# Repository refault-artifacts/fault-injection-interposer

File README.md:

# Interposer PCB for DDR5 UDIMMs
Hardware files for the fault injection interposer of
REFault: A Fault Injection Platform for Rowhammer Research on DDR5 Memory.

The interposer consists of a 6-layer PCB that can be used in between an off-the-shelf
DDR5-compatible motherboard and an DDR5 SDRAM UDIMM. Some signals
can be forced high or low by an external control signal to inject
or suppress certain DRAM commands.

## Design
The schematic and PCB was designed in KiCAD. Open `hardware/udimm_interposer.kicad_pro` in KiCAD 8 or later to view the design files.
From there, you should be able to select the schematic and PCB layout.

For convenience, you can also find a PDF version of the schematic in `docs/schematic.pdf`. A bill of materials (BOM) is also provided in `docs`.

## Manufacturing
The PCBs were manufactured by JLCPCB and were assembled by hand.
It is reasonable to also order an SMT stencil, so soldering is easier.
The Gerber files needed for manufacturing are located at `hardware/output`.

### Impedance Control
The PCB is impedance controlled. It uses the JLC06121H-1080 stackup options.

### Manufacturing options
| Option | Value |
|--------|-------|
|Base Material| FR-4|
|Layers| 6|
|Dimension| 133.4 mm * 21.9 mm|
|Product Type| Industrial/Consumer electronics|
|Different Design| 1|
|Delivery Format| Single PCB|
|PCB Thickness| 1.2|
|Impedance Control| yes JLC06121H-1080|
|Layer Sequence||
|PCB Color| Green|
|Silkscreen| White|
|Via Covering| Tented|
|Surface Finish| ENIG|
|Deburring/Edge rounding| No|
|Outer Copper Weight| 1|
|Inner Copper Weight| 0.5|
|Gold Fingers| Yes|
|Flying Probe Test|Fully Test|
|Castellated Holes|no|
|Remove Order Number|No|
|Min hole size/diameter|0.3/0.4mm|
|4-Wire Kelvin Test|No|
|Material Type|FR4-Standard TG 135-140|
|Paper between PCBs|No|
|Appearance Quality|IPC Class 2 Standard|
|Confirm Production file|Yes|
|Silkscreen Technology|Ink-jet/Screen Printing Silkscreen|
|Package Box|With JLCPCB logo|

**Important**: For future orders, it may be a better idea to not select "Gold Fingers",
because we do not want chamfering along the edge connector. As far as
the PCB manufacturer is concerned, the edge connector consists of normal
pads. Otherwise add an explicit remark that you do not want any chamfering.

## Assembly
Assembly can be done manually using a stencil (ordered with the PCB),
some solder paste and a hot air gun. The connector on top was soldered
manually.
### Bill of Materials (BOM)
See docs/bom

### Verification
To ensure that there are no shorts between pins and all pins are properly
soldered, a continuity check should be performed prior to testing
the module more thoroughly with e.g. Memtest86+.

## Known Issuses
Since the UDIMM connector is comparatively long, the PCB might experience
thermal warping along the length of the connector, lifting the PCB away
from the connectors of the DIMM. For this reason, the connector was soldered
on manually.

### Modifications
Some switches are not connected to the flat flex connector.
To hard-wire them to the "passthrough" position, a wire must be soldered
to the appropriate pads on the voltage regulator side of the PCB.
Check the schematic and design files for details.

## License
Some parts of the PCB may be subject to copyright of third parties
(e.g. 3D models provided by manufacturer).
Otherwise, the design is released under MIT License.

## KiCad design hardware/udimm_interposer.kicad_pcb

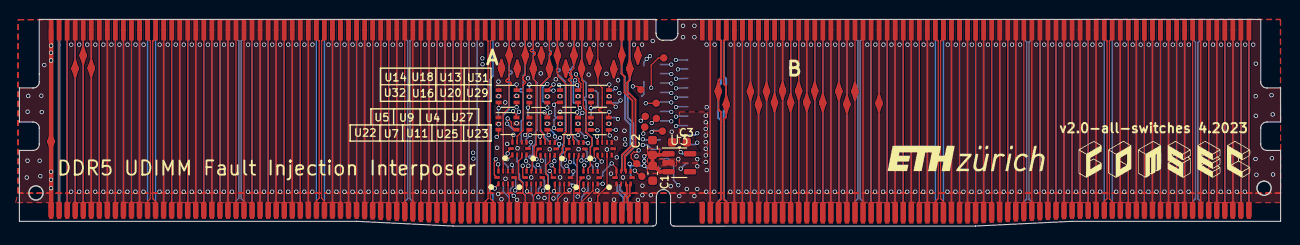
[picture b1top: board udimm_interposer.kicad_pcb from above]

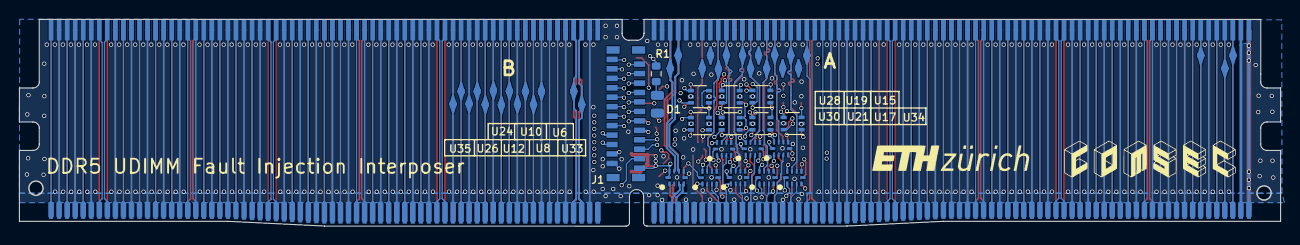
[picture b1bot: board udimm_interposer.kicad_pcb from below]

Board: 6 copper layers, 133.3 x 21.9 mm, 119 parts (50 on the bottom side), 225 nets.

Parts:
C1, C3: 100n; C_0603_1608Metric
C2: 2.2u; C_0603_1608Metric
D1: APHCM2012CGCK-F01; LED_0805_2012Metric
J1: Molex 5019512430; 5019512430
R1: 330; R_0603_1608Metric
TP1: VIN_BULK; testpoint
TP2: HSCL; testpoint
TP3: HSDA; testpoint
TP4, TP6, TP9, TP12, TP15, TP17, TP20, TP23, TP27, TP43, TP46, TP49, TP50, TP52, TP54, TP55, TP58, TP61, TP64, TP67, TP69, TP81, TP82: VSS; testpoint
TP5: CS0_A_n; testpoint
TP7: CA0_A; testpoint
TP8: CA2_A; testpoint
TP10: CA4_A; testpoint
TP11: CA6_A; testpoint
TP13: CA8_A; testpoint
TP14: CA10_A; testpoint
TP16: CA12_A; testpoint
TP18: CK0_A_t; testpoint
TP19: CK0_A_c; testpoint
TP21: CK0_B_t; testpoint
TP22: CK0_B_c; testpoint
TP24: CA12_B; testpoint
TP25: CA10_B; testpoint
TP26: CA8_B; testpoint
TP28: CA6_B; testpoint
TP29: CA4_B; testpoint
TP30: CA2_B; testpoint
TP31: CA0_B; testpoint
TP32: CS0_B_n; testpoint
TP34: RESET_n; testpoint
TP35: PWR_GD; testpoint
TP36: HSA; testpoint
TP38: PWR_EN; testpoint
TP39: ALERT_n; testpoint
TP40: CS1_A_n; testpoint
TP41: CA1_A; testpoint
TP42: CA3_A; testpoint
TP44: CA5_A; testpoint
TP45: CA7_A; testpoint
TP47: CA9_A; testpoint
TP48: CA11_A; testpoint
TP51: CK1_A_t; testpoint
TP53: CK1_A_c; testpoint
TP56: CK1_B_t; testpoint
TP57: CK1_B_c; testpoint
TP59: CA11_B; testpoint
TP60: CA9_B; testpoint
TP62: CA7_B; testpoint
TP63: CA5_B; testpoint
TP65: CA3_B; testpoint
TP66: CA1_B; testpoint
TP68: CS1_B_n; testpoint
TP70, TP71, TP83, TP84, TP85, TP86, TP87, TP88, TP89: tp; testpoint_small
U1: DDR5; ddr5_edge_connector
U2: UMAX 90414-15011-21; ddr5_bottom_conn_double
U3: TLV71211_SOT23-5; SOT-23-5
U4, U5, U6, U7, U8, U9, U10, U11, U12, U22, U23, U24, U25, U26, U27, U33, U35: TMUX136; uqfn10
U13, U14, U15, U16, U17, U18, U19, U20, U21, U28, U29, U30, U31, U32, U34: SOT-363_SC-70-6

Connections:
+1V1: C3.1, U3.5 (OUT), U13.3 (B0), U14.3 (B0), U15.3 (B0), U16.3 (B0), U17.3 (B0), U18.3 (B0), U19.3 (B0), U20.3 (B0), U21.3 (B0), U28.3 (B0), U29.3 (B0), U30.3 (B0), U31.3 (B0), U32.3 (B0), U34.3 (B0)
+3.3V: C1.1, C2.1, J1.1, R1.1, U3.1 (IN), U3.3 (EN), U4.10 (VCC), U5.10 (VCC), U6.10 (VCC), U7.10 (VCC), U8.10 (VCC), U9.10 (VCC), U10.10 (VCC), U11.10 (VCC), U12.10 (VCC), U13.5 (VCC), U14.5 (VCC), U15.5 (VCC), U16.5 (VCC), U17.5 (VCC), U18.5 (VCC), U19.5 (VCC), U20.5 (VCC), U21.5 (VCC), U22.10 (VCC), U23.9 (SEL), U23.10 (VCC), U24.10 (VCC), U25.10 (VCC), U26.10 (VCC), U27.10 (VCC), U28.5 (VCC), U29.5 (VCC), U30.5 (VCC), U31.5 (VCC), U32.5 (VCC), U33.10 (VCC), U34.5 (VCC), U35.9 (SEL), U35.10 (VCC)
ALERT_n_DIMM: TP39.1, U1.200 (ALERT_n), U2.200 (ALERT_n)
CA0_A_DIMM: TP7.1, U2.60 (CA0_A), U5.8 (COM1)
CA0_A_HOST: U1.60 (CA0_A), U5.3 (B1)
CA0_B_DIMM: TP31.1, U1.91 (CA0_B), U2.91 (CA0_B)
CA0_DISC: J1.9, TP71.1, U5.9 (SEL)
CA0_STATIC: J1.24, U14.6 (S)
CA1_A_DIMM: TP41.1, U2.204 (CA1_A), U6.8 (COM1)
CA1_A_HOST: U1.204 (CA1_A), U6.3 (B1)
CA1_B_DIMM: TP66.1, U1.235 (CA1_B), U2.235 (CA1_B)
CA1_DISC: J1.7, U6.9 (SEL)
CA1_STATIC: J1.23, U15.6 (S)
CA2_A_DIMM: TP8.1, U2.61 (CA2_A), U7.8 (COM1)
CA2_A_HOST: U1.61 (CA2_A), U7.3 (B1)
CA2_B_DIMM: TP30.1, U1.90 (CA2_B), U2.90 (CA2_B)
CA2_DISC: J1.16, U7.9 (SEL)
CA2_STATIC: J1.10, U16.6 (S)
CA3_A_DIMM: TP42.1, U2.205 (CA3_A), U8.8 (COM1)
CA3_A_HOST: U1.205 (CA3_A), U8.3 (B1)
CA3_B_DIMM: TP65.1, U1.234 (CA3_B), U2.234 (CA3_B)
CA3_DISC: J1.17, U8.9 (SEL)
CA3_STATIC: J1.19, U17.6 (S)
CA4_A_DIMM: TP10.1, U2.63 (CA4_A), U9.8 (COM1)
CA4_A_HOST: U1.63 (CA4_A), U9.3 (B1)
CA4_B_DIMM: TP29.1, U1.88 (CA4_B), U2.88 (CA4_B)
CA4_DISC: J1.14, U9.9 (SEL)
CA4_STATIC: J1.22, U18.6 (S)
CA5_A_DIMM: TP44.1, U2.207 (CA5_A), U10.8 (COM1)
CA5_A_HOST: U1.207 (CA5_A), U10.3 (B1)
CA5_B_DIMM: TP63.1, U1.232 (CA5_B), U2.232 (CA5_B)
CA5_DISC: J1.8, U10.9 (SEL)
CA5_STATIC: J1.21, U19.6 (S)
CA6_A_DIMM: TP11.1, U2.64 (CA6_A), U11.8 (COM1)
CA6_A_HOST: U1.64 (CA6_A), U11.3 (B1)
CA6_B_DIMM: TP28.1, U1.87 (CA6_B), U2.87 (CA6_B)
CA6_DISC: J1.18, U11.9 (SEL)
CA6_STATIC: J1.12, U20.6 (S)
CA7_A_DIMM: TP45.1, U2.208 (CA7_A), U12.8 (COM1)
CA7_A_HOST: U1.208 (CA7_A), U12.3 (B1)
CA7_B_DIMM: TP62.1, U1.231 (CA7_B), U2.231 (CA7_B)
CA7_DISC: J1.3, U12.9 (SEL)
CA7_STATIC: J1.5, U21.6 (S)
CA8_A_DIMM: TP13.1, U2.66 (CA8_A), U4.8 (COM1)
CA8_A_HOST: U1.66 (CA8_A), U4.3 (B1)
CA8_B_DIMM: TP26.1, U1.85 (CA8_B), U2.85 (CA8_B)
CA8_DISC: J1.4, U4.9 (SEL)
CA8_STATIC: J1.20, U13.6 (S)
CA9_A_DIMM: TP47.1, U2.210 (CA9_A), U24.8 (COM1)
CA9_A_HOST: U1.210 (CA9_A), U24.3 (B1)
CA9_B_DIMM: TP60.1, U1.229 (CA9_B), U2.229 (CA9_B)
CA9_DISC: TP83.1, U24.9 (SEL)
CA9_STATIC: TP70.1, U28.6 (S)
CA10_A_DIMM: TP14.1, U2.67 (CA10_A), U25.8 (COM1)
CA10_A_HOST: U1.67 (CA10_A), U25.3 (B1)
CA10_B_DIMM: TP25.1, U1.84 (CA10_B), U2.84 (CA10_B)
CA10_DISC: J1.6, U25.9 (SEL)
CA10_STATIC: J1.11, U29.6 (S)
CA11_A_DIMM: TP48.1, U2.211 (CA11_A), U26.8 (COM1)
CA11_A_HOST: U1.211 (CA11_A), U26.3 (B1)
CA11_B_DIMM: TP59.1, U1.228 (CA11_B), U2.228 (CA11_B)
CA11_DISC: TP84.1, U26.9 (SEL)
CA11_STATIC: TP86.1, U30.6 (S)
CA12_A_DIMM: TP16.1, U2.69 (CA12_A), U27.8 (COM1)
CA12_A_HOST: U1.69 (CA12_A), U27.3 (B1)
CA12_B_DIMM: TP24.1, U1.82 (CA12_B), U2.82 (CA12_B)
CA12_DISC: TP85.1, U27.9 (SEL)
CA12_STATIC: TP87.1, U31.6 (S)
CB0_A_DIMM: U1.51 (CB0_A), U2.51 (CB0_A)
CB0_B_DIMM: U1.97 (CB0_B), U2.97 (CB0_B)
CB1_A_DIMM: U1.53 (CB1_A), U2.53 (CB1_A)
CB1_B_DIMM: U1.99 (CB1_B), U2.99 (CB1_B)
CB2_A_DIMM: U1.196 (CB2_A), U2.196 (CB2_A)
CB2_B_DIMM: U1.242 (CB2_B), U2.242 (CB2_B)
CB3_A_DIMM: U1.198 (CB3_A), U2.198 (CB3_A)
CB3_B_DIMM: U1.244 (CB3_B), U2.244 (CB3_B)
CK0_A_DIMM_N: TP19.1, U2.73 (CK0_A_c), U23.7 (COM2)
CK0_A_DIMM_P: TP18.1, U2.72 (CK0_A_t), U23.8 (COM1)
CK0_A_HOST_N: U1.73 (CK0_A_c), U23.4 (B2)
CK0_A_HOST_P: U1.72 (CK0_A_t), U23.3 (B1)
CK0_B_DIMM_N: TP22.1, U1.79 (CK0_B_c), U2.79 (CK0_B_c)
CK0_B_DIMM_P: TP21.1, U1.78 (CK0_B_t), U2.78 (CK0_B_t)
CK1_A_DIMM_N: TP53.1, U2.217 (CK1_A_c), U35.8 (COM1)
CK1_A_DIMM_P: TP51.1, U2.216 (CK1_A_t), U35.7 (COM2)
CK1_A_HOST_N: U1.217 (CK1_A_c), U35.3 (B1)
CK1_A_HOST_P: U1.216 (CK1_A_t), U35.4 (B2)
CK1_B_DIMM_N: TP57.1, U1.223 (CK1_B_c), U2.223 (CK1_B_c)
CK1_B_DIMM_P: TP56.1, U1.222 (CK1_B_t), U2.222 (CK1_B_t)
CS0_A_n_DIMM: TP5.1, U2.58 (CS0_A_n), U22.8 (COM1)
CS0_A_n_HOST: U1.58 (CS0_A_n), U22.3 (B1)
CS0_B_n_DIMM: TP32.1, U1.93 (CS0_B_n), U2.93 (CS0_B_n)
CS0_DISC: J1.15, U22.9 (SEL)
CS0_STATIC: J1.13, U32.6 (S)
CS1_A_n_DIMM: TP40.1, U2.202 (CS1_A_n), U33.8 (COM1)
CS1_A_n_HOST: U1.202 (CS1_A_n), U33.3 (B1)
CS1_B_n_DIMM: TP68.1, U1.237 (CS1_B_n), U2.237 (CS1_B_n)
CS1_DISC: TP88.1, U33.9 (SEL)
CS1_STATIC: TP89.1, U34.6 (S)
DM0_A_n_DIMM: U1.158 (DM0_A_n), U2.158 (DM0_A_n)
DM0_B_n_DIMM: U1.250 (DM0_B_n), U2.250 (DM0_B_n)
DM1_A_n_DIMM: U1.24 (DM1_A_n), U2.24 (DM1_A_n)
DM1_B_n_DIMM: U1.116 (DM1_B_n), U2.116 (DM1_B_n)
DM2_A_n_DIMM: U1.179 (DM2_A_n), U2.179 (DM2_A_n)
DM2_B_n_DIMM: U1.271 (DM2_B_n), U2.271 (DM2_B_n)
DM3_A_n_DIMM: U1.45 (DM3_A_n), U2.45 (DM3_A_n)
DM3_B_n_DIMM: U1.137 (DM3_B_n), U2.137 (DM3_B_n)
DQ0_A_DIMM: U1.9 (DQ0_A), U2.9 (DQ0_A)
DQ0_B_DIMM: U1.101 (DQ0_B), U2.101 (DQ0_B)
DQ1_A_DIMM: U1.11 (DQ1_A), U2.11 (DQ1_A)
DQ1_B_DIMM: U1.103 (DQ1_B), U2.103 (DQ1_B)
DQ2_A_DIMM: U1.154 (DQ2_A), U2.154 (DQ2_A)
DQ2_B_DIMM: U1.246 (DQ2_B), U2.246 (DQ2_B)
DQ3_A_DIMM: U1.156 (DQ3_A), U2.156 (DQ3_A)
DQ3_B_DIMM: U1.248 (DQ3_B), U2.248 (DQ3_B)
DQ4_A_DIMM: U1.16 (DQ4_A), U2.16 (DQ4_A)
DQ4_B_DIMM: U1.108 (DQ4_B), U2.108 (DQ4_B)
DQ5_A_DIMM: U1.18 (DQ5_A), U2.18 (DQ5_A)
DQ5_B_DIMM: U1.110 (DQ5_B), U2.110 (DQ5_B)
DQ6_A_DIMM: U1.160 (DQ6_A), U2.160 (DQ6_A)
DQ6_B_DIMM: U1.252 (DQ6_B), U2.252 (DQ6_B)
DQ7_A_DIMM: U1.162 (DQ7_A), U2.162 (DQ7_A)
DQ7_B_DIMM: U1.254 (DQ7_B), U2.254 (DQ7_B)
DQ8_A_DIMM: U1.20 (DQ8_A), U2.20 (DQ8_A)
DQ8_B_DIMM: U1.112 (DQ8_B), U2.112 (DQ8_B)
DQ9_A_DIMM: U1.22 (DQ9_A), U2.22 (DQ9_A)
DQ9_B_DIMM: U1.114 (DQ9_B), U2.114 (DQ9_B)
DQ10_A_DIMM: U1.164 (DQ10_A), U2.164 (DQ10_A)
DQ10_B_DIMM: U1.256 (DQ10_B), U2.256 (DQ10_B)
DQ11_A_DIMM: U1.166 (DQ11_A), U2.166 (DQ11_A)
DQ11_B_DIMM: U1.258 (DQ11_B), U2.258 (DQ11_B)
DQ12_A_DIMM: U1.26 (DQ12_A), U2.26 (DQ12_A)
DQ12_B_DIMM: U1.118 (DQ12_B), U2.118 (DQ12_B)
DQ13_A_DIMM: U1.28 (DQ13_A), U2.28 (DQ13_A)
DQ13_B_DIMM: U1.120 (DQ13_B), U2.120 (DQ13_B)
DQ14_A_DIMM: U1.171 (DQ14_A), U2.171 (DQ14_A)
DQ14_B_DIMM: U1.263 (DQ14_B), U2.263 (DQ14_B)
DQ15_A_DIMM: U1.173 (DQ15_A), U2.173 (DQ15_A)
DQ15_B_DIMM: U1.265 (DQ15_B), U2.265 (DQ15_B)
DQ16_A_DIMM: U1.30 (DQ16_A), U2.30 (DQ16_A)
DQ16_B_DIMM: U1.122 (DQ16_B), U2.122 (DQ16_B)
DQ17B_DIMM: U1.124 (DQ17_B), U2.124 (DQ17_B)
DQ17_A_DIMM: U1.32 (DQ17_A), U2.32 (DQ17_A)
DQ18_A_DIMM: U1.175 (DQ18_A), U2.175 (DQ18_A)
DQ18_B_DIMM: U1.267 (DQ18_B), U2.267 (DQ18_B)
DQ19_A_DIMM: U1.177 (DQ19_A), U2.177 (DQ19_A)
DQ19_B_DIMM: U1.269 (DQ19_B), U2.269 (DQ19_B)
DQ20_A_DIMM: U1.37 (DQ20_A), U2.37 (DQ20_A)
DQ20_B_DIMM: U1.129 (DQ20_B), U2.129 (DQ20_B)
DQ21_A_DIMM: U1.39 (DQ21_A), U2.39 (DQ21_A)
DQ21_B_DIMM: U1.131 (DQ21_B), U2.131 (DQ21_B)
DQ22_A_DIMM: U1.181 (DQ22_A), U2.181 (DQ22_A)
DQ22_B_DIMM: U1.273 (DQ22_B), U2.273 (DQ22_B)
DQ23_A_DIMM: U1.183 (DQ23_A), U2.183 (DQ23_A)
DQ23_B_DIMM: U1.275 (DQ23_B), U2.275 (DQ23_B)
DQ24_A_DIMM: U1.41 (DQ24_A), U2.41 (DQ24_A)
DQ24_B_DIMM: U1.133 (DQ24_B), U2.133 (DQ24_B)
DQ25_A_DIMM: U1.43 (DQ25_A), U2.43 (DQ25_A)
DQ25_B_DIMM: U1.135 (DQ25_B), U2.135 (DQ25_B)
DQ26_A_DIMM: U1.185 (DQ26_A), U2.185 (DQ26_A)
DQ26_B_DIMM: U1.277 (DQ26_B), U2.277 (DQ26_B)
DQ27_A_DIMM: U1.187 (DQ27_A), U2.187 (DQ27_A)
DQ27_B_DIMM: U1.279 (DQ27_B), U2.279 (DQ27_B)
DQ28_A_DIMM: U1.47 (DQ28_A), U2.47 (DQ28_A)
DQ28_B_DIMM: U1.139 (DQ28_B), U2.139 (DQ28_B)
DQ29_A_DIMM: U1.49 (DQ29_A), U2.49 (DQ29_A)
DQ29_B_DIMM: U1.141 (DQ29_B), U2.141 (DQ29_B)
DQ30_A_DIMM: U1.192 (DQ30_A), U2.192 (DQ30_A)
DQ30_B_DIMM: U1.284 (DQ30_B), U2.284 (DQ30_B)
DQ31_A_DIMM: U1.194 (DQ31_A), U2.194 (DQ31_A)
DQ31_B_DIMM: U1.286 (DQ31_B), U2.286 (DQ31_B)
DQS0_A_DIMM_N: U1.13 (DQS0_A_c), U2.13 (DQS0_A_c)
DQS0_A_DIMM_P: U1.14 (DQS0_A_t), U2.14 (DQS0_A_t)
DQS0_B_DIMM_N: U1.105 (DQS0_B_c), U2.105 (DQS0_B_c)
DQS0_B_DIMM_P: U1.106 (DQS0_B_t), U2.106 (DQS0_B_t)
DQS1_A_DIMM_N: U1.168 (DQS1_A_c), U2.168 (DQS1_A_c)
DQS1_A_DIMM_P: U1.169 (DQS1_A_t), U2.169 (DQS1_A_t)
DQS1_B_DIMM_N: U1.260 (DQS1_B_c), U2.260 (DQS1_B_c)
DQS1_B_DIMM_P: U1.261 (DQS1_B_t), U2.261 (DQS1_B_t)
DQS2_A_DIMM_N: U1.34 (DQS2_A_c), U2.34 (DQS2_A_c)
DQS2_A_DIMM_P: U1.35 (DQS2_A_t), U2.35 (DQS2_A_t)
DQS2_B_DIMM_N: U1.126 (DQS2_B_c), U2.126 (DQS2_B_c)
DQS2_B_DIMM_P: U1.127 (DQS2_B_t), U2.127 (DQS2_B_t)
DQS3_A_DIMM_N: U1.189 (DQS3_A_c), U2.189 (DQS3_A_c)
DQS3_A_DIMM_P: U1.190 (DQS3_A_t), U2.190 (DQS3_A_t)
DQS3_B_DIMM_N: U1.281 (DQS3_B_c), U2.281 (DQS3_B_c)
DQS3_B_DIMM_P: U1.282 (DQS3_B_t), U2.282 (DQS3_B_t)
DQS4_A_DIMM_N: U1.55 (DQS4_A_c), U2.55 (DQS4_A_c)
DQS4_A_DIMM_P: U1.56 (DQS4_A_t), U2.56 (DQS4_A_t)
DQS4_B_DIMM_N: U1.239 (DQS4_B_c), U2.239 (DQS4_B_c)
DQS4_B_DIMM_P: U1.240 (DQS4_B_t), U2.240 (DQS4_B_t)
HSA_DIMM: TP36.1, U1.148 (HSA), U2.148 (HSA)
HSCL_DIMM: TP2.1, U1.4 (HSCL), U2.4 (HSCL)
HSDA_DIMM: TP3.1, U1.5 (HSDA), U2.5 (HSDA)
unnamed: D1.2 (A), R1.2
unnamed: U10.1 (A1), U19.4 (A)
unnamed: U11.1 (A1), U20.4 (A)
unnamed: U12.1 (A1), U21.4 (A)
unnamed: U4.1 (A1), U13.4 (A)
unnamed: U5.1 (A1), U14.4 (A)
unnamed: U6.1 (A1), U15.4 (A)
unnamed: U7.1 (A1), U16.4 (A)
unnamed: U8.1 (A1), U17.4 (A)
unnamed: U9.1 (A1), U18.4 (A)
unnamed: U22.1 (A1), U32.4 (A)
unnamed: U24.1 (A1), U28.4 (A)
unnamed: U25.1 (A1), U29.4 (A)
unnamed: U26.1 (A1), U30.4 (A)
unnamed: U27.1 (A1), U31.4 (A)
unnamed: U33.1 (A1), U34.4 (A)
PWR_EN_DIMM: TP38.1, U1.151 (PWR_EN), U2.151 (PWR_EN)
PWR_GOOD_DIMM: TP35.1, U1.147 (PWR_GOOD), U2.147 (PWR_GOOD)
RESET_n_DIMM: TP34.1, U1.95 (RESET_n), U2.95 (RESET_n)
RFU2_DIMM: U1.2 (RFU), U2.2 (RFU)
RFU3_DIMM: U1.3 (RFU), U2.3 (RFU)
RFU7_DIMM: U1.7 (RFU), U2.7 (RFU)
RFU81_DIMM: U1.81 (RFU), U2.81 (RFU)
RFU143_DIMM: U1.143 (RFU), U2.143 (RFU)
RFU144_DIMM: U1.144 (RFU), U2.144 (RFU)
RFU149_DIMM: U1.149 (RFU), U2.149 (RFU)
RFU152_DIMM: U1.152 (RFU), U2.152 (RFU)
RFU225_DIMM: U1.225 (RFU), U2.225 (RFU)
RFU226_DIMM: U1.226 (RFU), U2.226 (RFU)
RFU288_DIMM: U1.288 (RFU), U2.288 (RFU)
VIN_BULK_DIMM: TP1.1, U1.1 (VIN_BULK), U1.145 (VIN_BULK), U1.146 (VIN_BULK), U2.1 (VIN_BULK), U2.145 (VIN_BULK), U2.146 (VIN_BULK)
VSS: C1.2, C2.2, C3.2, D1.1 (K), J1.2, TP4.1, TP6.1, TP9.1, TP12.1, TP15.1, TP17.1, TP20.1, TP23.1, TP27.1, TP43.1, TP46.1, TP49.1, TP50.1, TP52.1, TP54.1, TP55.1, TP58.1, TP61.1, TP64.1, TP67.1, TP69.1, TP81.1, TP82.1, U1.6 (VSS), U1.8 (VSS), U1.10 (VSS), U1.12 (VSS), U1.15 (VSS), U1.17 (VSS), U1.19 (VSS), U1.21 (VSS), U1.23 (VSS), U1.25 (VSS), U1.27 (VSS), U1.29 (VSS), U1.31 (VSS), U1.33 (VSS), U1.36 (VSS), U1.38 (VSS), U1.40 (VSS), U1.42 (VSS), U1.44 (VSS), U1.46 (VSS), U1.48 (VSS), U1.50 (VSS), U1.52 (VSS), U1.54 (VSS), U1.57 (VSS), U1.59 (VSS), U1.62 (VSS), U1.65 (VSS), U1.68 (VSS), U1.71 (VSS), U1.74 (VSS), U1.77 (VSS), U1.80 (VSS), U1.83 (VSS), U1.86 (VSS), U1.89 (VSS), U1.92 (VSS), U1.94 (VSS), U1.96 (VSS), U1.98 (VSS), U1.100 (VSS), U1.102 (VSS), U1.104 (VSS), U1.107 (VSS), U1.109 (VSS), U1.111 (VSS), U1.113 (VSS), U1.115 (VSS), U1.117 (VSS), U1.119 (VSS), U1.121 (VSS), U1.123 (VSS), U1.125 (VSS), U1.128 (VSS), U1.130 (VSS), U1.132 (VSS), U1.134 (VSS), U1.136 (VSS), U1.138 (VSS), U1.140 (VSS), U1.142 (VSS), U1.150 (VSS), U1.153 (VSS), U1.155 (VSS), U1.157 (VSS), U1.159 (VSS), U1.161 (VSS), U1.163 (VSS), U1.165 (VSS), U1.167 (VSS), U1.170 (VSS), U1.172 (VSS), U1.174 (VSS), U1.176 (VSS), U1.178 (VSS), U1.180 (VSS), U1.182 (VSS), U1.184 (VSS), U1.186 (VSS), U1.188 (VSS), U1.191 (VSS), U1.193 (VSS), U1.195 (VSS), U1.197 (VSS), U1.199 (VSS), U1.201 (VSS), U1.203 (VSS), U1.206 (VSS), U1.209 (VSS), U1.212 (VSS), U1.215 (VSS), U1.218 (VSS), U1.221 (VSS), U1.224 (VSS), U1.227 (VSS), U1.230 (VSS), U1.233 (VSS), U1.236 (VSS), U1.238 (VSS), U1.241 (VSS), U1.243 (VSS), U1.245 (VSS), U1.247 (VSS), U1.249 (VSS), U1.251 (VSS), U1.253 (VSS), U1.255 (VSS), U1.257 (VSS), U1.259 (VSS), U1.262 (VSS), U1.264 (VSS), U1.266 (VSS), U1.268 (VSS), U1.270 (VSS), U1.272 (VSS), U1.274 (VSS), U1.276 (VSS), U1.278 (VSS), U1.280 (VSS), U1.283 (VSS), U1.285 (VSS), U1.287 (VSS), U2.6 (VSS), U2.8 (VSS), U2.10 (VSS), U2.12 (VSS), U2.15 (VSS), U2.17 (VSS), U2.19 (VSS), U2.21 (VSS), U2.23 (VSS), U2.25 (VSS), U2.27 (VSS), U2.29 (VSS), U2.31 (VSS), U2.33 (VSS), U2.36 (VSS), U2.38 (VSS), U2.40 (VSS), U2.42 (VSS), U2.44 (VSS), U2.46 (VSS), U2.48 (VSS), U2.50 (VSS), U2.52 (VSS), U2.54 (VSS), U2.57 (VSS), U2.59 (VSS), U2.62 (VSS), U2.65 (VSS), U2.68 (VSS), U2.71 (VSS), U2.74 (VSS), U2.77 (VSS), U2.80 (VSS), U2.83 (VSS), U2.86 (VSS), U2.89 (VSS), U2.92 (VSS), U2.94 (VSS), U2.96 (VSS), U2.98 (VSS), U2.100 (VSS), U2.102 (VSS), U2.104 (VSS), U2.107 (VSS), U2.109 (VSS), U2.111 (VSS), U2.113 (VSS), U2.115 (VSS), U2.117 (VSS), U2.119 (VSS), U2.121 (VSS), U2.123 (VSS), U2.125 (VSS), U2.128 (VSS), U2.130 (VSS), U2.132 (VSS), U2.134 (VSS), U2.136 (VSS), U2.138 (VSS), U2.140 (VSS), U2.142 (VSS), U2.150 (VSS), U2.153 (VSS), U2.155 (VSS), U2.157 (VSS), U2.159 (VSS), U2.161 (VSS), U2.163 (VSS), U2.165 (VSS), U2.167 (VSS), U2.170 (VSS), U2.172 (VSS), U2.174 (VSS), U2.176 (VSS), U2.178 (VSS), U2.180 (VSS), U2.182 (VSS), U2.184 (VSS), U2.186 (VSS), U2.188 (VSS), U2.191 (VSS), U2.193 (VSS), U2.195 (VSS), U2.197 (VSS), U2.199 (VSS), U2.201 (VSS), U2.203 (VSS), U2.206 (VSS), U2.209 (VSS), U2.212 (VSS), U2.215 (VSS), U2.218 (VSS), U2.221 (VSS), U2.224 (VSS), U2.227 (VSS), U2.230 (VSS), U2.233 (VSS), U2.236 (VSS), U2.238 (VSS), U2.241 (VSS), U2.243 (VSS), U2.245 (VSS), U2.247 (VSS), U2.249 (VSS), U2.251 (VSS), U2.253 (VSS), U2.255 (VSS), U2.257 (VSS), U2.259 (VSS), U2.262 (VSS), U2.264 (VSS), U2.266 (VSS), U2.268 (VSS), U2.270 (VSS), U2.272 (VSS), U2.274 (VSS), U2.276 (VSS), U2.278 (VSS), U2.280 (VSS), U2.283 (VSS), U2.285 (VSS), U2.287 (VSS), U3.2 (GND), U4.2 (A2), U4.4 (B2), U4.5 (GND), U4.6 (/EN), U4.7 (COM2), U5.2 (A2), U5.4 (B2), U5.5 (GND), U5.6 (/EN), U5.7 (COM2), U6.2 (A2), U6.4 (B2), U6.5 (GND), U6.6 (/EN), U6.7 (COM2), U7.2 (A2), U7.4 (B2), U7.5 (GND), U7.6 (/EN), U7.7 (COM2), U8.2 (A2), U8.4 (B2), U8.5 (GND), U8.6 (/EN), U8.7 (COM2), U9.2 (A2), U9.4 (B2), U9.5 (GND), U9.6 (/EN), U9.7 (COM2), U10.2 (A2), U10.4 (B2), U10.5 (GND), U10.6 (/EN), U10.7 (COM2), U11.2 (A2), U11.4 (B2), U11.5 (GND), U11.6 (/EN), U11.7 (COM2), U12.2 (A2), U12.4 (B2), U12.5 (GND), U12.6 (/EN), U12.7 (COM2), U13.1 (B1), U13.2 (GND), U14.1 (B1), U14.2 (GND), U15.1 (B1), U15.2 (GND), U16.1 (B1), U16.2 (GND), U17.1 (B1), U17.2 (GND), U18.1 (B1), U18.2 (GND), U19.1 (B1), U19.2 (GND), U20.1 (B1), U20.2 (GND), U21.1 (B1), U21.2 (GND), U22.2 (A2), U22.4 (B2), U22.5 (GND), U22.6 (/EN), U22.7 (COM2), U23.1 (A1), U23.2 (A2), U23.5 (GND), U23.6 (/EN), U24.2 (A2), U24.4 (B2), U24.5 (GND), U24.6 (/EN), U24.7 (COM2), U25.2 (A2), U25.4 (B2), U25.5 (GND), U25.6 (/EN), U25.7 (COM2), U26.2 (A2), U26.4 (B2), U26.5 (GND), U26.6 (/EN), U26.7 (COM2), U27.2 (A2), U27.4 (B2), U27.5 (GND), U27.6 (/EN), U27.7 (COM2), U28.1 (B1), U28.2 (GND), U29.1 (B1), U29.2 (GND), U30.1 (B1), U30.2 (GND), U31.1 (B1), U31.2 (GND), U32.1 (B1), U32.2 (GND), U33.2 (A2), U33.4 (B2), U33.5 (GND), U33.6 (/EN), U33.7 (COM2), U34.1 (B1), U34.2 (GND), U35.1 (A1), U35.2 (A2), U35.5 (GND), U35.6 (/EN)

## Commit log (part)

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2025-02-08 feat: add design files
2025-02-19 docs(readme): minor fixes
